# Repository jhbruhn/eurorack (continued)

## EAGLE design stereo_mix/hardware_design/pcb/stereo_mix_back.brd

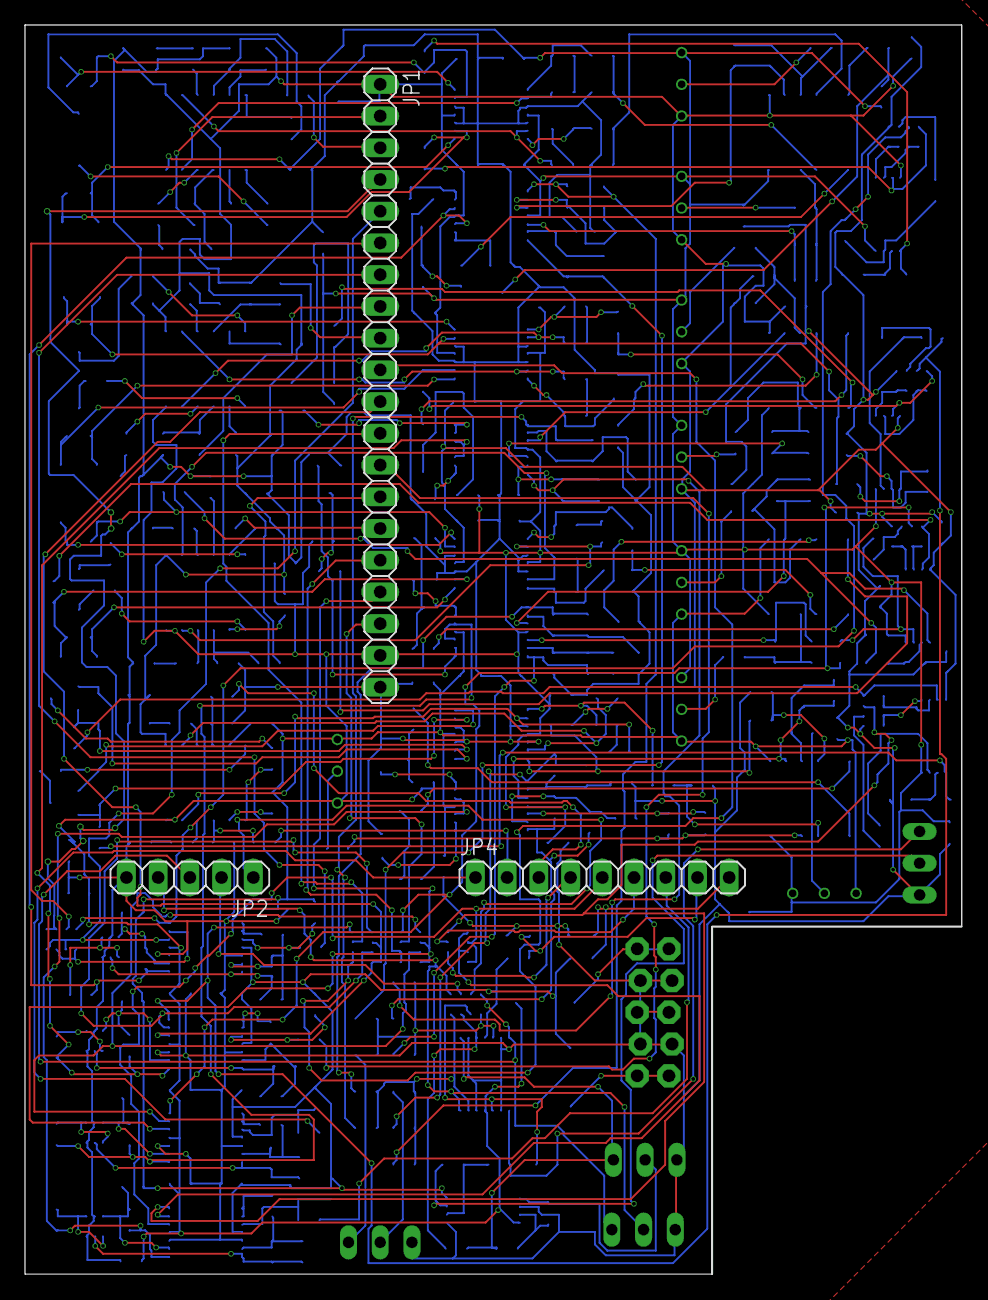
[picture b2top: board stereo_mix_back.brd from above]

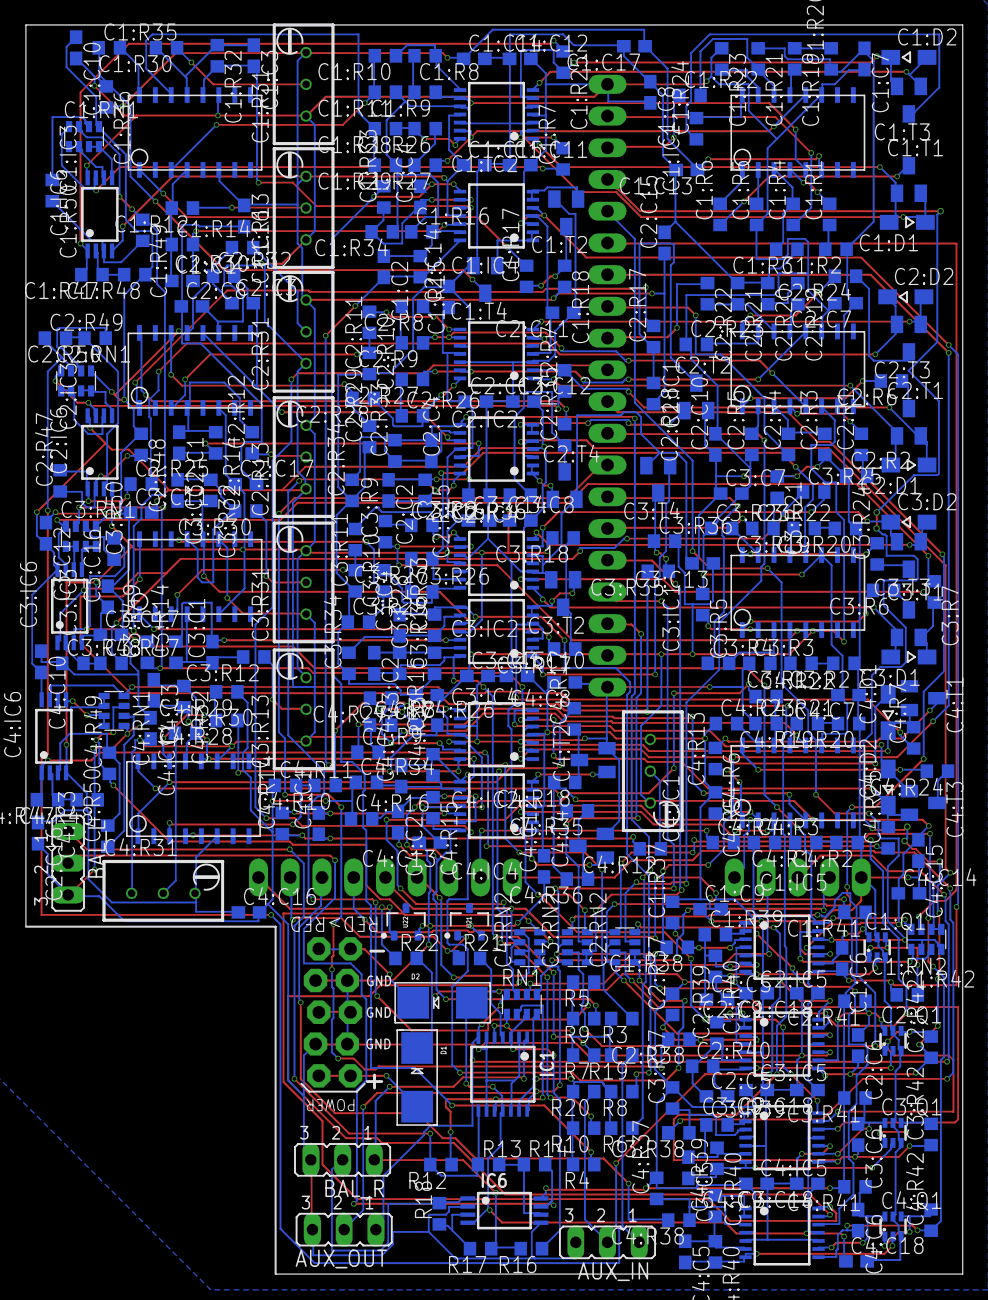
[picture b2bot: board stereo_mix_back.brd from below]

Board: 2 copper layers, 75.0 x 100.0 mm, 349 parts (346 on the bottom side), 271 nets.

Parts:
AUX_IN: JP2
AUX_OUT: JP2
BAL_L: JP2
BAL_R: JP2
C1:C1, C1:C3, C1:C5, C1:C6, C2:C1, C2:C3, C2:C5, C2:C6, C3:C1, C3:C3, C3:C5, C3:C6, C4:C1, C4:C3, C4:C5, C4:C6: 100pF; C0603
C1:C2, C1:C4, C2:C2, C2:C4, C3:C2, C3:C4, C4:C2, C4:C4: 22pF; C0603
C1:C7, C1:C8, C1:C9, C1:C10, C1:C11, C1:C12, C1:C13, C1:C14, C1:C15, C1:C16, C1:C17, C1:C18, C2:C7, C2:C8, C2:C9, C2:C10, C2:C11, C2:C12, C2:C13, C2:C14, C2:C15, C2:C16, C2:C17, C2:C18, C3:C7, C3:C8, C3:C9, C3:C10, C3:C11, C3:C12, C3:C13, C3:C14, C3:C15, C3:C16, C3:C17, C3:C18, C4:C7, C4:C8, C4:C9, C4:C10, C4:C11, C4:C12, C4:C13, C4:C14, C4:C15, C4:C16, C4:C17, C4:C18: 100nF; C0603
C1:D1, C1:D2, C2:D1, C2:D2, C3:D1, C3:D2, C4:D1, C4:D2: 1N4148; SOD323-W
C1:IC1, C1:IC3, C2:IC1, C2:IC3, C3:IC1, C3:IC3, C4:IC1, C4:IC3: LM13700; DMP16
C1:IC2, C1:IC4, C1:IC5, C2:IC2, C2:IC4, C2:IC5, C3:IC2, C3:IC4, C3:IC5, C4:IC2, C4:IC4, C4:IC5: TL084PW; TSSOP14
C1:IC6, C2:IC6, C3:IC6, C4:IC6: TL082PW; TSSOP8
C1:Q1, C2:Q1, C3:Q1, C4:Q1: BC847BS; SOT363_PHILIPS
C1:R1, C1:R19, C2:R1, C2:R19, C3:R1, C3:R19, C4:R1, C4:R19: 22; R0603
C1:R2, C1:R20, C2:R2, C2:R20, C3:R2, C3:R20, C4:R2, C4:R20: 470; R0603
C1:R3, C1:R21, C2:R3, C2:R21, C3:R3, C3:R21, C4:R3, C4:R21: 510; R0603
C1:R4, C1:R22, C2:R4, C2:R22, C3:R4, C3:R22, C4:R4, C4:R22: 21k; R0603
C1:R5, C1:R23, C2:R5, C2:R23, C3:R5, C3:R23, C4:R5, C4:R23: 12k; R0603
C1:R6, C1:R24, C2:R6, C2:R24, C3:R6, C3:R24, C4:R6, C4:R24: 7k2; R0603
C1:R7, C1:R25, C2:R7, C2:R25, C3:R7, C3:R25, C4:R7, C4:R25: 6k8; R0603
C1:R8, C1:R26, C2:R8, C2:R26, C3:R8, C3:R26, C4:R8, C4:R26: 560; R0603
C1:R9, C1:R17, C1:R27, C1:R35, C2:R9, C2:R17, C2:R27, C2:R35, C3:R9, C3:R17, C3:R27, C3:R35, C4:R9, C4:R17, C4:R27, C4:R35: 15k; R0603
C1:R10, C1:R15, C1:R28, C1:R33, C1:R49, C1:R50, C2:R10, C2:R15, C2:R28, C2:R33, C2:R49, C2:R50, C3:R10, C3:R15, C3:R28, C3:R33, C3:R49, C3:R50, C4:R10, C4:R15, C4:R28, C4:R33, C4:R49, C4:R50: 100k; R0603
C1:R11, C1:R29, C2:R11, C2:R29, C3:R11, C3:R29, C4:R11, C4:R29: 680; R0603
C1:R12, C1:R30, C1:R37, C1:R39, C2:R12, C2:R30, C2:R37, C2:R39, C3:R12, C3:R30, C3:R37, C3:R39, C4:R12, C4:R30, C4:R37, C4:R39: 1M; R0603
C1:R13, C1:R31, C2:R13, C2:R31, C3:R13, C3:R31, C4:R13, C4:R31: 100k; RTRIMT93YA
C1:R14, C1:R32, C2:R14, C2:R32, C3:R14, C3:R32, C4:R14, C4:R32: 47k; R0603
C1:R16, C1:R34, C2:R16, C2:R34, C3:R16, C3:R34, C4:R16, C4:R34: 68k; R0603
C1:R18, C1:R36, C2:R18, C2:R36, C3:R18, C3:R36, C4:R18, C4:R36: 680k; R0603
C1:R38, C2:R38, C3:R38, C4:R38: 1k; R0603
C1:R40, C2:R40, C3:R40, C4:R40: 10k; R0603
C1:R41, C2:R41, C3:R41, C4:R41: 10M; R0603
C1:R42, C2:R42, C3:R42, C4:R42: 1k5; R0603
C1:R47, C1:R48, C2:R47, C2:R48, C3:R47, C3:R48, C4:R47, C4:R48: 200k; R0603
C1:RN1, C1:RN2, C2:RN1, C2:RN2, C3:RN1, C3:RN2, C4:RN1, C4:RN2: CTS742C083
C1:T1, C1:T2, C1:T3, C1:T4, C2:T1, C2:T2, C2:T3, C2:T4, C3:T1, C3:T2, C3:T3, C3:T4, C4:T1, C4:T2, C4:T3, C4:T4: 3906; SOT23-BEC
C5: EURO_POWER_LOCKFAT-LOCK; EURO_PWR_HEADER_LOCK
D1, D2: 1N4001; SMADIODE
IC1: TL084PW; TSSOP14
IC6: TL082PW; TSSOP8
JP1: 1X20
JP2: 1X05
JP4: 1X09
R3, R4, R5, R6, R7, R8, R9, R10, R13, R14, R17, R18, R19, R20: 100k; R0603
R12, R16: 24k; R0603
R21: R0603
R22: 680R; R0603
RN1: CTS742C083
U21: TEXAS_INSTRUMENTS_LM4040C5IDBZR; TEXAS_INSTRUMENTS_LM4040C5IDBZR_0
U22: TEXAS_INSTRUMENTS_LM4040C10IDBZR; TEXAS_INSTRUMENTS_LM4040C5IDBZR_0

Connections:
1_IN_L: C1:R4.1, JP1.2
1_IN_R: C1:R22.1, JP1.3
1_PAN_ATT_R: C1:RN2.3, JP1.6
1_PAN_ATT_W: C1:IC5.12, C1:RN2.6, C1:RN2.8, JP1.5
1_PAN_CV_IN: C1:RN2.1, C1:RN2.2, JP1.4
1_VOLUME_CV: C1:R38.2, JP1.7
2_IN_L: C2:R4.1, JP1.8
2_IN_R: C2:R22.1, JP1.9
2_PAN_ATT_R: C2:RN2.3, JP1.12
2_PAN_ATT_W: C2:IC5.12, C2:RN2.6, C2:RN2.8, JP1.11
2_PAN_CV_IN: C2:RN2.1, C2:RN2.2, JP1.10
2_VOLUME_CV: C2:R38.2, JP1.13
3_IN_L: C3:R4.1, JP1.14
3_IN_R: C3:R22.1, JP1.15
3_PAN_ATT_R: C3:RN2.3, JP1.18
3_PAN_ATT_W: C3:IC5.12, C3:RN2.6, C3:RN2.8, JP1.17
3_PAN_CV_IN: C3:RN2.1, C3:RN2.2, JP1.16
3_VOLUME_CV: C3:R38.2, JP4.1
4_IN_L: C4:R4.1, JP4.2
4_IN_R: C4:R22.1, JP4.3
4_PAN_ATT_R: C4:RN2.3, JP4.6
4_PAN_ATT_W: C4:IC5.12, C4:RN2.6, C4:RN2.8, JP4.5
4_PAN_CV_IN: C4:RN2.1, C4:RN2.2, JP4.4
4_VOLUME_CV: C4:R38.2, JP4.7
+12V: C1:C7.2, C1:C8.2, C1:C9.2, C1:C10.2, C1:C11.2, C1:C12.2, C1:IC1.P$11, C1:IC2.4, C1:IC3.P$11, C1:IC4.4, C1:IC5.4, C1:IC6.8, C1:R5.1, C1:R13.1, C1:R23.1, C1:R31.1, C1:R37.2, C1:R41.2, C2:C7.2, C2:C8.2, C2:C9.2, C2:C10.2, C2:C11.2, C2:C12.2, C2:IC1.P$11, C2:IC2.4, C2:IC3.P$11, C2:IC4.4, C2:IC5.4, C2:IC6.8, C2:R5.1, C2:R13.1, C2:R23.1, C2:R31.1, C2:R37.2, C2:R41.2, C3:C7.2, C3:C8.2, C3:C9.2, C3:C10.2, C3:C11.2, C3:C12.2, C3:IC1.P$11, C3:IC2.4, C3:IC3.P$11, C3:IC4.4, C3:IC5.4, C3:IC6.8, C3:R5.1, C3:R13.1, C3:R23.1, C3:R31.1, C3:R37.2, C3:R41.2, C4:C7.2, C4:C8.2, C4:C9.2, C4:C10.2, C4:C11.2, C4:C12.2, C4:IC1.P$11, C4:IC2.4, C4:IC3.P$11, C4:IC4.4, C4:IC5.4, C4:IC6.8, C4:R5.1, C4:R13.1, C4:R23.1, C4:R31.1, C4:R37.2, C4:R41.2, D1.C, IC1.4, IC6.8, JP1.1, R21.2, R22.2
-12V: C1:C13.1, C1:C14.1, C1:C15.1, C1:C16.1, C1:C17.1, C1:C18.1, C1:IC1.P$6, C1:IC2.11, C1:IC3.P$6, C1:IC4.11, C1:IC5.11, C1:IC6.4, C1:R13.3, C1:R18.2, C1:R31.3, C1:R36.2, C2:C13.1, C2:C14.1, C2:C15.1, C2:C16.1, C2:C17.1, C2:C18.1, C2:IC1.P$6, C2:IC2.11, C2:IC3.P$6, C2:IC4.11, C2:IC5.11, C2:IC6.4, C2:R13.3, C2:R18.2, C2:R31.3, C2:R36.2, C3:C13.1, C3:C14.1, C3:C15.1, C3:C16.1, C3:C17.1, C3:C18.1, C3:IC1.P$6, C3:IC2.11, C3:IC3.P$6, C3:IC4.11, C3:IC5.11, C3:IC6.4, C3:R13.3, C3:R18.2, C3:R31.3, C3:R36.2, C4:C13.1, C4:C14.1, C4:C15.1, C4:C16.1, C4:C17.1, C4:C18.1, C4:IC1.P$6, C4:IC2.11, C4:IC3.P$6, C4:IC4.11, C4:IC5.11, C4:IC6.4, C4:R13.3, C4:R18.2, C4:R31.3, C4:R36.2, D2.A, IC1.11, IC6.4, JP1.19
AUX_IN_L: AUX_IN.1, R19.1
AUX_IN_R: AUX_IN.2, R20.1
BAL_N_L: BAL_L.2, IC6.7, R14.2
BAL_N_R: BAL_R.2, IC6.1, R18.2
BAL_P_L: BAL_L.1, IC1.8, R12.2, R13.1
BAL_P_R: BAL_R.1, IC1.1, R16.2, R17.1
BYPASS_L: AUX_OUT.1, IC1.7, JP2.3, RN1.8
BYPASS_R: AUX_OUT.2, IC1.14, JP2.4, RN1.5
C1:N$1: C1:IC1.P$4, C1:R1.2
C1:N$2: C1:R1.1, C1:R2.2
C1:N$3: C1:IC1.P$3, C1:R3.2, C1:R4.2
C1:N$4: C1:IC1.P$1, C1:R6.2
C1:N$5: C1:IC1.P$2, C1:R5.2
C1:N$6: C1:R6.1, C1:T1.C
C1:N$7: C1:D1.A, C1:IC2.1, C1:T1.B
C1:N$8: C1:D1.C, C1:IC2.2, C1:R7.2, C1:T1.E
C1:N$9: C1:IC1.P$5, C1:IC2.9, C1:R9.1
C1:N$10: C1:R8.1, C1:R9.2
C1:N$11: C1:IC2.8, C1:R8.2, C1:R10.1
C1:N$12: C1:C1.1, C1:IC3.P$4, C1:R12.2, C1:R14.1
C1:N$13: C1:IC3.P$3, C1:R10.2, C1:R11.2
C1:N$14: C1:R12.1, C1:R13.2
C1:N$15: C1:C2.1, C1:IC4.13, C1:R15.1, C1:R16.2
C1:N$16: C1:C1.2, C1:IC4.12, C1:R14.2
C1:N$17: C1:IC3.P$1, C1:R17.2
C1:N$18: C1:R17.1, C1:R18.1, C1:T2.C
C1:N$19: C1:IC4.6, C1:IC4.7, C1:T2.B
C1:N$20: C1:IC1.P$13, C1:R19.2
C1:N$21: C1:R19.1, C1:R20.2
C1:N$22: C1:IC1.P$14, C1:R21.2, C1:R22.2
C1:N$23: C1:IC1.P$15, C1:R23.2
C1:N$24: C1:IC1.P$16, C1:R24.2
C1:N$25: C1:R24.1, C1:T3.C
C1:N$26: C1:D2.A, C1:IC2.7, C1:T3.B
C1:N$27: C1:D2.C, C1:IC2.6, C1:R25.2, C1:T3.E
C1:N$28: C1:IC1.P$12, C1:IC2.13, C1:R27.1
C1:N$29: C1:R26.1, C1:R27.2
C1:N$30: C1:IC2.14, C1:R26.2, C1:R28.1
C1:N$31: C1:IC3.P$14, C1:R28.2, C1:R29.2
C1:N$32: C1:C3.1, C1:IC3.P$13, C1:R30.2, C1:R32.1
C1:N$33: C1:R30.1, C1:R31.2
C1:N$34: C1:C3.2, C1:IC3.P$12, C1:IC4.10, C1:R32.2
C1:N$35: C1:C4.1, C1:IC4.9, C1:R33.1, C1:R34.2
C1:N$36: C1:IC3.P$16, C1:R35.2
C1:N$37: C1:R35.1, C1:R36.1, C1:T4.C
C1:N$38: C1:IC4.1, C1:IC4.2, C1:T4.B
C1:N$39: C1:IC5.1, C1:IC5.2, C1:R39.2
C1:N$40: C1:IC5.3, C1:R37.1, C1:R38.1
C1:N$41: C1:C5.1, C1:IC5.6, C1:R39.1, C1:R40.1
C1:N$42: C1:C5.2, C1:IC5.7, C1:Q1.2, C1:R40.2
C1:N$43: C1:IC6.5, C1:RN1.3, C1:RN1.4
C1:N$44: C1:C6.1, C1:IC5.9, C1:Q1.6, C1:R41.1
C1:N$45: C1:IC6.6, C1:RN1.1, C1:RN1.2
C1:N$46: C1:Q1.1, C1:Q1.4, C1:R42.2
C1:N$47: C1:IC6.2, C1:R47.1, C1:R48.2
C1:N$48: C1:IC5.13, C1:RN2.5, C1:RN2.7
C1:N$50: C1:IC6.3, C1:R49.2, C1:R50.2
C1:PAN_CV: C1:IC5.14, C1:R49.1, C1:RN1.7, C1:RN2.4
C1:PAN_CV_L: C1:IC6.7, C1:R7.1, C1:RN1.8
C1:PAN_CV_R: C1:IC6.1, C1:R25.1, C1:R47.2
C1:REF_5: C1:R50.1, C1:RN1.6
C1:VOLUME_CV_LOG: C1:C6.2, C1:IC4.3, C1:IC4.5, C1:IC5.8, C1:R42.1
C2:N$1: C2:IC1.P$4, C2:R1.2
C2:N$2: C2:R1.1, C2:R2.2
C2:N$3: C2:IC1.P$3, C2:R3.2, C2:R4.2
C2:N$4: C2:IC1.P$1, C2:R6.2
C2:N$5: C2:IC1.P$2, C2:R5.2
C2:N$6: C2:R6.1, C2:T1.C
C2:N$7: C2:D1.A, C2:IC2.1, C2:T1.B
C2:N$8: C2:D1.C, C2:IC2.2, C2:R7.2, C2:T1.E
C2:N$9: C2:IC1.P$5, C2:IC2.9, C2:R9.1
C2:N$10: C2:R8.1, C2:R9.2
C2:N$11: C2:IC2.8, C2:R8.2, C2:R10.1
C2:N$12: C2:C1.1, C2:IC3.P$4, C2:R12.2, C2:R14.1
C2:N$13: C2:IC3.P$3, C2:R10.2, C2:R11.2
C2:N$14: C2:R12.1, C2:R13.2
C2:N$15: C2:C2.1, C2:IC4.13, C2:R15.1, C2:R16.2
C2:N$16: C2:C1.2, C2:IC4.12, C2:R14.2
C2:N$17: C2:IC3.P$1, C2:R17.2
C2:N$18: C2:R17.1, C2:R18.1, C2:T2.C
C2:N$19: C2:IC4.6, C2:IC4.7, C2:T2.B
C2:N$20: C2:IC1.P$13, C2:R19.2
C2:N$21: C2:R19.1, C2:R20.2
C2:N$22: C2:IC1.P$14, C2:R21.2, C2:R22.2
C2:N$23: C2:IC1.P$15, C2:R23.2
C2:N$24: C2:IC1.P$16, C2:R24.2
C2:N$25: C2:R24.1, C2:T3.C
C2:N$26: C2:D2.A, C2:IC2.7, C2:T3.B
C2:N$27: C2:D2.C, C2:IC2.6, C2:R25.2, C2:T3.E
C2:N$28: C2:IC1.P$12, C2:IC2.13, C2:R27.1
C2:N$29: C2:R26.1, C2:R27.2
C2:N$30: C2:IC2.14, C2:R26.2, C2:R28.1
C2:N$31: C2:IC3.P$14, C2:R28.2, C2:R29.2
C2:N$32: C2:C3.1, C2:IC3.P$13, C2:R30.2, C2:R32.1
C2:N$33: C2:R30.1, C2:R31.2
C2:N$34: C2:C3.2, C2:IC3.P$12, C2:IC4.10, C2:R32.2
C2:N$35: C2:C4.1, C2:IC4.9, C2:R33.1, C2:R34.2
C2:N$36: C2:IC3.P$16, C2:R35.2
C2:N$37: C2:R35.1, C2:R36.1, C2:T4.C
C2:N$38: C2:IC4.1, C2:IC4.2, C2:T4.B
C2:N$39: C2:IC5.1, C2:IC5.2, C2:R39.2
C2:N$40: C2:IC5.3, C2:R37.1, C2:R38.1
C2:N$41: C2:C5.1, C2:IC5.6, C2:R39.1, C2:R40.1
C2:N$42: C2:C5.2, C2:IC5.7, C2:Q1.2, C2:R40.2
C2:N$43: C2:IC6.5, C2:RN1.3, C2:RN1.4
C2:N$44: C2:C6.1, C2:IC5.9, C2:Q1.6, C2:R41.1
C2:N$45: C2:IC6.6, C2:RN1.1, C2:RN1.2
C2:N$46: C2:Q1.1, C2:Q1.4, C2:R42.2
C2:N$47: C2:IC6.2, C2:R47.1, C2:R48.2
C2:N$48: C2:IC5.13, C2:RN2.5, C2:RN2.7
C2:N$50: C2:IC6.3, C2:R49.2, C2:R50.2
C2:PAN_CV: C2:IC5.14, C2:R49.1, C2:RN1.7, C2:RN2.4
C2:PAN_CV_L: C2:IC6.7, C2:R7.1, C2:RN1.8
C2:PAN_CV_R: C2:IC6.1, C2:R25.1, C2:R47.2
C2:REF_5: C2:R50.1, C2:RN1.6
C2:VOLUME_CV_LOG: C2:C6.2, C2:IC4.3, C2:IC4.5, C2:IC5.8, C2:R42.1
C3:N$1: C3:IC1.P$4, C3:R1.2
C3:N$2: C3:R1.1, C3:R2.2
C3:N$3: C3:IC1.P$3, C3:R3.2, C3:R4.2
C3:N$4: C3:IC1.P$1, C3:R6.2
C3:N$5: C3:IC1.P$2, C3:R5.2
C3:N$6: C3:R6.1, C3:T1.C
C3:N$7: C3:D1.A, C3:IC2.1, C3:T1.B
C3:N$8: C3:D1.C, C3:IC2.2, C3:R7.2, C3:T1.E
C3:N$9: C3:IC1.P$5, C3:IC2.9, C3:R9.1
C3:N$10: C3:R8.1, C3:R9.2
C3:N$11: C3:IC2.8, C3:R8.2, C3:R10.1
C3:N$12: C3:C1.1, C3:IC3.P$4, C3:R12.2, C3:R14.1
C3:N$13: C3:IC3.P$3, C3:R10.2, C3:R11.2
C3:N$14: C3:R12.1, C3:R13.2
C3:N$15: C3:C2.1, C3:IC4.13, C3:R15.1, C3:R16.2
C3:N$16: C3:C1.2, C3:IC4.12, C3:R14.2
C3:N$17: C3:IC3.P$1, C3:R17.2
C3:N$18: C3:R17.1, C3:R18.1, C3:T2.C
C3:N$19: C3:IC4.6, C3:IC4.7, C3:T2.B
C3:N$20: C3:IC1.P$13, C3:R19.2
C3:N$21: C3:R19.1, C3:R20.2
C3:N$22: C3:IC1.P$14, C3:R21.2, C3:R22.2
C3:N$23: C3:IC1.P$15, C3:R23.2
C3:N$24: C3:IC1.P$16, C3:R24.2
C3:N$25: C3:R24.1, C3:T3.C
C3:N$26: C3:D2.A, C3:IC2.7, C3:T3.B
C3:N$27: C3:D2.C, C3:IC2.6, C3:R25.2, C3:T3.E
C3:N$28: C3:IC1.P$12, C3:IC2.13, C3:R27.1
C3:N$29: C3:R26.1, C3:R27.2
C3:N$30: C3:IC2.14, C3:R26.2, C3:R28.1
C3:N$31: C3:IC3.P$14, C3:R28.2, C3:R29.2
C3:N$32: C3:C3.1, C3:IC3.P$13, C3:R30.2, C3:R32.1
C3:N$33: C3:R30.1, C3:R31.2
C3:N$34: C3:C3.2, C3:IC3.P$12, C3:IC4.10, C3:R32.2
C3:N$35: C3:C4.1, C3:IC4.9, C3:R33.1, C3:R34.2
C3:N$36: C3:IC3.P$16, C3:R35.2
C3:N$37: C3:R35.1, C3:R36.1, C3:T4.C
C3:N$38: C3:IC4.1, C3:IC4.2, C3:T4.B
C3:N$39: C3:IC5.1, C3:IC5.2, C3:R39.2
C3:N$40: C3:IC5.3, C3:R37.1, C3:R38.1
C3:N$41: C3:C5.1, C3:IC5.6, C3:R39.1, C3:R40.1
C3:N$42: C3:C5.2, C3:IC5.7, C3:Q1.2, C3:R40.2
C3:N$43: C3:IC6.5, C3:RN1.3, C3:RN1.4
C3:N$44: C3:C6.1, C3:IC5.9, C3:Q1.6, C3:R41.1
C3:N$45: C3:IC6.6, C3:RN1.1, C3:RN1.2
C3:N$46: C3:Q1.1, C3:Q1.4, C3:R42.2
C3:N$47: C3:IC6.2, C3:R47.1, C3:R48.2
C3:N$48: C3:IC5.13, C3:RN2.5, C3:RN2.7
C3:N$50: C3:IC6.3, C3:R49.2, C3:R50.2
C3:PAN_CV: C3:IC5.14, C3:R49.1, C3:RN1.7, C3:RN2.4
C3:PAN_CV_L: C3:IC6.7, C3:R7.1, C3:RN1.8
C3:PAN_CV_R: C3:IC6.1, C3:R25.1, C3:R47.2
C3:REF_5: C3:R50.1, C3:RN1.6
C3:VOLUME_CV_LOG: C3:C6.2, C3:IC4.3, C3:IC4.5, C3:IC5.8, C3:R42.1
C4:N$1: C4:IC1.P$4, C4:R1.2
C4:N$2: C4:R1.1, C4:R2.2
C4:N$3: C4:IC1.P$3, C4:R3.2, C4:R4.2
C4:N$4: C4:IC1.P$1, C4:R6.2
C4:N$5: C4:IC1.P$2, C4:R5.2
C4:N$6: C4:R6.1, C4:T1.C
C4:N$7: C4:D1.A, C4:IC2.1, C4:T1.B
C4:N$8: C4:D1.C, C4:IC2.2, C4:R7.2, C4:T1.E
C4:N$9: C4:IC1.P$5, C4:IC2.9, C4:R9.1
C4:N$10: C4:R8.1, C4:R9.2
C4:N$11: C4:IC2.8, C4:R8.2, C4:R10.1
C4:N$12: C4:C1.1, C4:IC3.P$4, C4:R12.2, C4:R14.1
C4:N$13: C4:IC3.P$3, C4:R10.2, C4:R11.2
C4:N$14: C4:R12.1, C4:R13.2
C4:N$15: C4:C2.1, C4:IC4.13, C4:R15.1, C4:R16.2
C4:N$16: C4:C1.2, C4:IC4.12, C4:R14.2
C4:N$17: C4:IC3.P$1, C4:R17.2
C4:N$18: C4:R17.1, C4:R18.1, C4:T2.C
C4:N$19: C4:IC4.6, C4:IC4.7, C4:T2.B
C4:N$20: C4:IC1.P$13, C4:R19.2
C4:N$21: C4:R19.1, C4:R20.2
C4:N$22: C4:IC1.P$14, C4:R21.2, C4:R22.2
C4:N$23: C4:IC1.P$15, C4:R23.2
C4:N$24: C4:IC1.P$16, C4:R24.2
C4:N$25: C4:R24.1, C4:T3.C
C4:N$26: C4:D2.A, C4:IC2.7, C4:T3.B
C4:N$27: C4:D2.C, C4:IC2.6, C4:R25.2, C4:T3.E
C4:N$28: C4:IC1.P$12, C4:IC2.13, C4:R27.1
C4:N$29: C4:R26.1, C4:R27.2
C4:N$30: C4:IC2.14, C4:R26.2, C4:R28.1
C4:N$31: C4:IC3.P$14, C4:R28.2, C4:R29.2
C4:N$32: C4:C3.1, C4:IC3.P$13, C4:R30.2, C4:R32.1
C4:N$33: C4:R30.1, C4:R31.2
C4:N$34: C4:C3.2, C4:IC3.P$12, C4:IC4.10, C4:R32.2
C4:N$35: C4:C4.1, C4:IC4.9, C4:R33.1, C4:R34.2
C4:N$36: C4:IC3.P$16, C4:R35.2
C4:N$37: C4:R35.1, C4:R36.1, C4:T4.C
C4:N$38: C4:IC4.1, C4:IC4.2, C4:T4.B
C4:N$39: C4:IC5.1, C4:IC5.2, C4:R39.2
C4:N$40: C4:IC5.3, C4:R37.1, C4:R38.1
C4:N$41: C4:C5.1, C4:IC5.6, C4:R39.1, C4:R40.1
C4:N$42: C4:C5.2, C4:IC5.7, C4:Q1.2, C4:R40.2
C4:N$43: C4:IC6.5, C4:RN1.3, C4:RN1.4
C4:N$44: C4:C6.1, C4:IC5.9, C4:Q1.6, C4:R41.1
C4:N$45: C4:IC6.6, C4:RN1.1, C4:RN1.2
C4:N$46: C4:Q1.1, C4:Q1.4, C4:R42.2
C4:N$47: C4:IC6.2, C4:R47.1, C4:R48.2
C4:N$48: C4:IC5.13, C4:RN2.5, C4:RN2.7
C4:N$50: C4:IC6.3, C4:R49.2, C4:R50.2
C4:PAN_CV: C4:IC5.14, C4:R49.1, C4:RN1.7, C4:RN2.4
C4:PAN_CV_L: C4:IC6.7, C4:R7.1, C4:RN1.8
C4:PAN_CV_R: C4:IC6.1, C4:R25.1, C4:R47.2
C4:REF_5: C4:R50.1, C4:RN1.6
C4:VOLUME_CV_LOG: C4:C6.2, C4:IC4.3, C4:IC4.5, C4:IC5.8, C4:R42.1
GND: AUX_IN.3, AUX_OUT.3, BAL_L.3, BAL_R.3, C1:C7.1, C1:C8.1, C1:C9.1, C1:C10.1, C1:C11.1, C1:C12.1, C1:C13.2, C1:C14.2, C1:C15.2, C1:C16.2, C1:C17.2, C1:C18.2, C1:IC2.3, C1:IC2.5, C1:IC2.10, C1:IC2.12, C1:IC5.5, C1:IC5.10, C1:Q1.3, C1:Q1.5, C1:R2.1, C1:R3.1, C1:R11.1, C1:R16.1, C1:R20.1, C1:R21.1, C1:R29.1, C1:R34.1, C1:R48.1, C1:RN1.5, C1:T2.E, C1:T4.E, C2:C7.1, C2:C8.1, C2:C9.1, C2:C10.1, C2:C11.1, C2:C12.1, C2:C13.2, C2:C14.2, C2:C15.2, C2:C16.2, C2:C17.2, C2:C18.2, C2:IC2.3, C2:IC2.5, C2:IC2.10, C2:IC2.12, C2:IC5.5, C2:IC5.10, C2:Q1.3, C2:Q1.5, C2:R2.1, C2:R3.1, C2:R11.1, C2:R16.1, C2:R20.1, C2:R21.1, C2:R29.1, C2:R34.1, C2:R48.1, C2:RN1.5, C2:T2.E, C2:T4.E, C3:C7.1, C3:C8.1, C3:C9.1, C3:C10.1, C3:C11.1, C3:C12.1, C3:C13.2, C3:C14.2, C3:C15.2, C3:C16.2, C3:C17.2, C3:C18.2, C3:IC2.3, C3:IC2.5, C3:IC2.10, C3:IC2.12, C3:IC5.5, C3:IC5.10, C3:Q1.3, C3:Q1.5, C3:R2.1, C3:R3.1, C3:R11.1, C3:R16.1, C3:R20.1, C3:R21.1, C3:R29.1, C3:R34.1, C3:R48.1, C3:RN1.5, C3:T2.E, C3:T4.E, C4:C7.1, C4:C8.1, C4:C9.1, C4:C10.1, C4:C11.1, C4:C12.1, C4:C13.2, C4:C14.2, C4:C15.2, C4:C16.2, C4:C17.2, C4:C18.2, C4:IC2.3, C4:IC2.5, C4:IC2.10, C4:IC2.12, C4:IC5.5, C4:IC5.10, C4:Q1.3, C4:Q1.5, C4:R2.1, C4:R3.1, C4:R11.1, C4:R16.1, C4:R20.1, C4:R21.1, C4:R29.1, C4:R34.1, C4:R48.1, C4:RN1.5, C4:T2.E, C4:T4.E, C5.GND1, C5.GND2, C5.GND3, C5.GND4, C5.GND5, C5.GND6, IC1.2, IC1.6, IC1.9, IC1.12, IC6.2, IC6.5, JP1.20, JP2.5, U21.2, U22.2
unnamed: C1:C2.2, C1:IC4.14, C1:R15.2, R3.1
unnamed: C1:C4.2, C1:IC4.8, C1:R33.2, R4.1
unnamed: IC1.10, R12.1, RN1.2
unnamed: C2:C2.2, C2:IC4.14, C2:R15.2, R5.1
unnamed: C2:C4.2, C2:IC4.8, C2:R33.2, R6.1
unnamed: C3:C2.2, C3:IC4.14, C3:R15.2, R7.1
unnamed: C3:C4.2, C3:IC4.8, C3:R33.2, R8.1
unnamed: C4:C2.2, C4:IC4.14, C4:R15.2, R9.1
unnamed: C4:C4.2, C4:IC4.8, C4:R33.2, R10.1
unnamed: IC1.3, R16.1, RN1.3
unnamed: IC6.3, R17.2, R18.1
unnamed: IC6.6, R13.2, R14.1
unnamed: C5.POS1, C5.POS2, D1.A
unnamed: C5.NEG1, C5.NEG2, D2.C
OUT_L: JP2.1, RN1.7
OUT_R: JP2.2, RN1.6
REF_5: JP4.8, R21.1, U21.1
REF_10: JP4.9, R22.1, U22.1
SUM_L: IC1.5, R3.2, R5.2, R7.2, R9.2, R19.2, RN1.1
SUM_R: IC1.13, R4.2, R6.2, R8.2, R10.2, R20.2, RN1.4

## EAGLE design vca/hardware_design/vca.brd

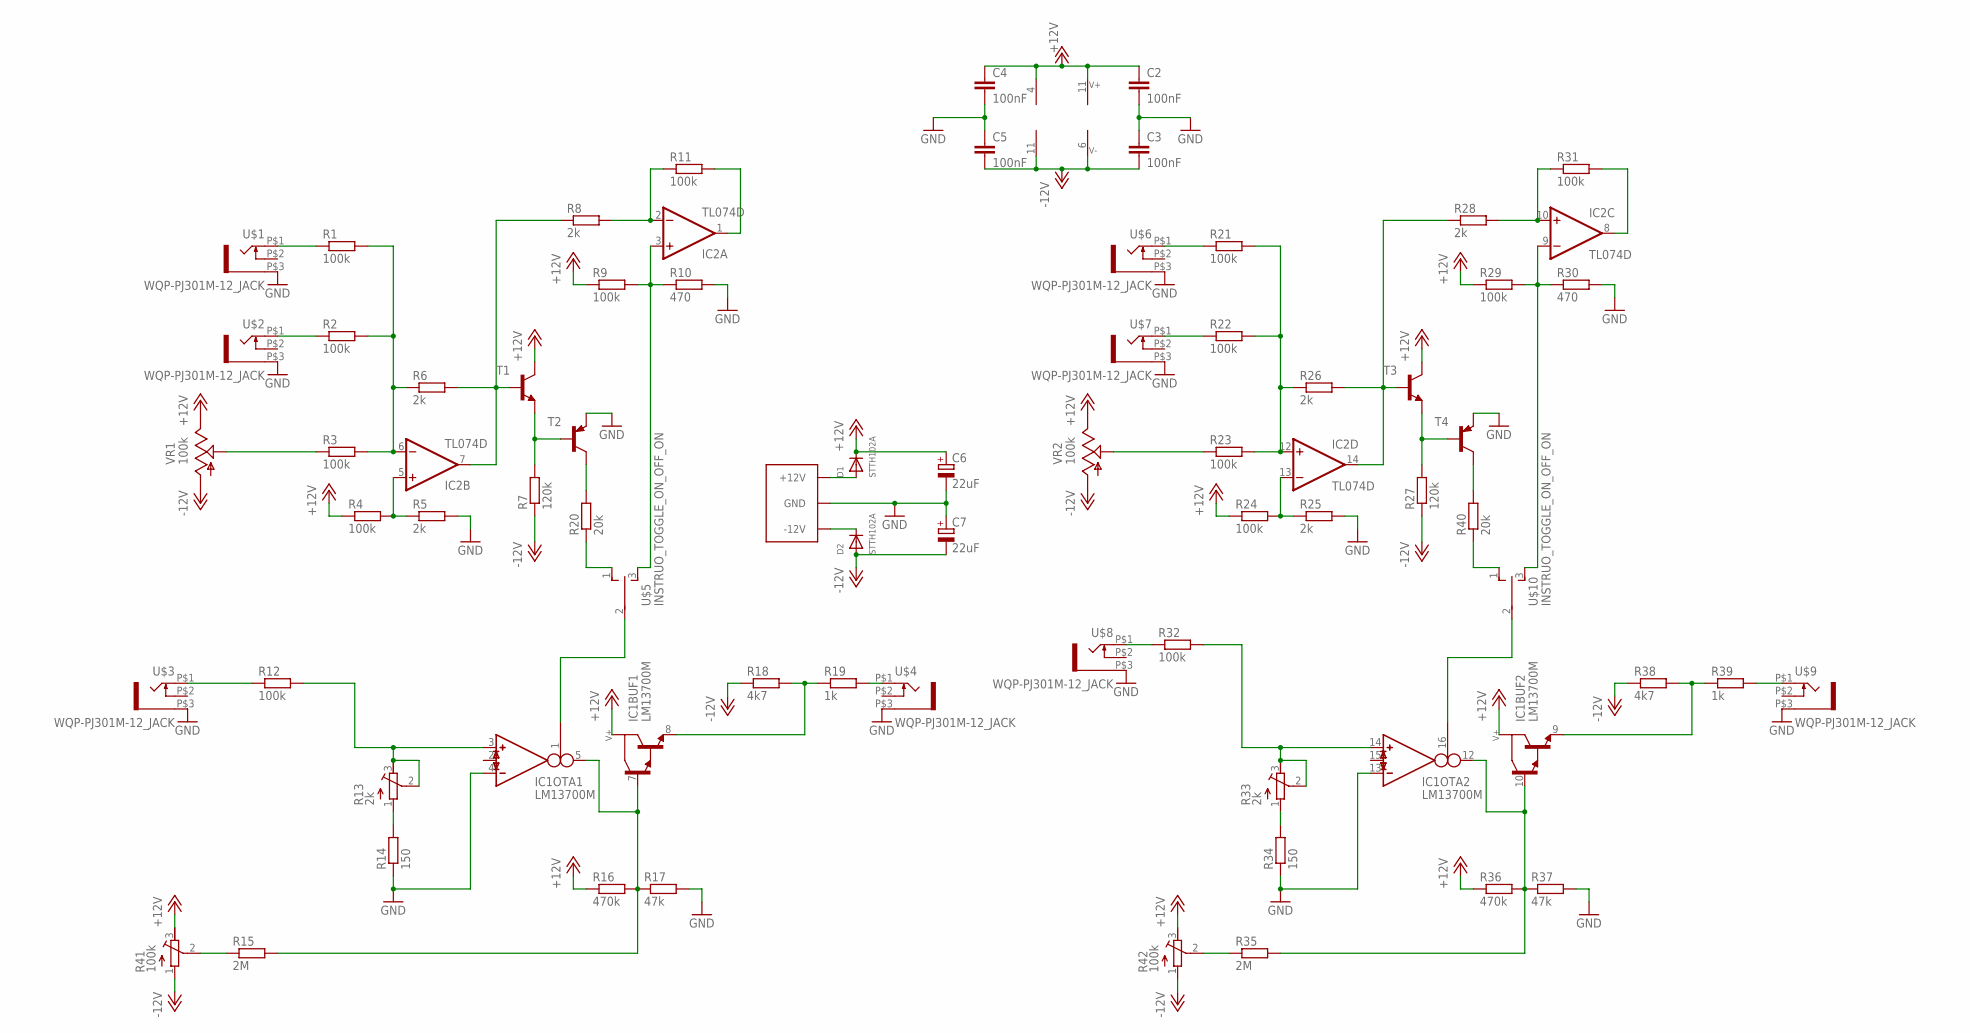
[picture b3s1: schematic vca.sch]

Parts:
C1: EURO_POWER_LOCKFAT-LOCK; EURO_PWR_HEADER_LOCK
C2, C3, C4, C5: 100nF; C0603
C6, C7: 22uF; PANASONIC_C
D1, D2: STTH102A; SMADIODE
IC1: LM13700M; SO16
IC2: TL074D; SO14
R1, R2, R3, R4, R9, R11, R12, R21, R22, R23, R24, R29, R31, R32: 100k; R0603
R5, R6, R8, R25, R26, R28: 2k; R0603
R7, R27: 120k; R0603
R10, R30: 470; R0603
R13, R33: 2k; RTRIM64W
R14, R34: 150; R0603
R15, R35: 2M; R0603
R16, R36: 470k; R0603
R17, R37: 47k; R0603
R18, R38: 4k7; R0603
R19, R39: 1k; R0603
R20, R40: 20k; R0603
R41, R42: 100k; RTRIM64W
T1, T3: MMBT3904LT1-NPN-SOT23-BEC; SOT23-BEC
T2, T4: MMBT3906LT1-PNP-SOT23-BEC; SOT23-BEC
U$1, U$2, U$3, U$4, U$6, U$7, U$8, U$9: WQP-PJ301M-12_JACK
U$5, U$10: INSTRUO_TOGGLE_ON_OFF_ON
VR1, VR2: 100k; 9MM_SNAP-IN_POT

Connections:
+12V: C2.1, C4.1, C6.+, D1.C, IC1.11 (V+), IC2.4 (V+), R4.1, R9.1, R16.1, R24.1, R29.1, R36.1, R41.3 (E), R42.3 (E), T1.C, T3.C, VR1.3 (E), VR2.3 (E)
-12V: C3.2, C5.2, C7.-, D2.A, IC1.6 (V-), IC2.11 (V-), R7.1, R18.1, R27.1, R38.1, R41.1 (A), R42.1 (A), VR1.1 (A), VR2.1 (A)
GND: C1.GND1 (GND), C1.GND2 (GND), C1.GND3 (GND), C1.GND4 (GND), C1.GND5 (GND), C1.GND6 (GND), C2.2, C3.1, C4.2, C5.1, C6.-, C7.+, IC1.4 (IN_N), IC1.13 (IN_N), R5.2, R10.2, R14.1, R17.2, R25.2, R30.2, R34.1, R37.2, T2.E, T4.E, U$1.P$3 (1), U$2.P$3 (1), U$3.P$3 (1), U$4.P$3 (1), U$6.P$3 (1), U$7.P$3 (1), U$8.P$3 (1), U$9.P$3 (1)
unnamed: R1.1, U$1.P$1 (2)
unnamed: R2.1, U$2.P$1 (2)
unnamed: R3.1, VR1.2 (S)
unnamed: IC2.6 (-IN), R1.2, R2.2, R3.2, R6.1
unnamed: IC2.5 (+IN), R4.2, R5.1
unnamed: IC2.7 (OUT), R6.2, R8.1, T1.B
unnamed: IC2.2 (-IN), R8.2, R11.1
unnamed: R7.2, T1.E, T2.B
unnamed: IC2.3 (+IN), R9.2, R10.1, U$5.3 (S)
unnamed: IC1.5 (OUT), IC1.7 (B), R15.2, R16.2, R17.1
unnamed: IC2.1 (OUT), R11.2
unnamed: R12.1, U$3.P$1 (2)
unnamed: IC1.3 (IN_P), R12.2, R13.2 (S), R13.3 (E)
unnamed: R15.1, R41.2 (S)
unnamed: R13.1 (A), R14.2
unnamed: R19.2, U$4.P$1 (2)
unnamed: IC1.8 (E), R18.2, R19.1
unnamed: R20.1, U$5.1 (O)
unnamed: IC1.1 (I_BIAS), U$5.2
unnamed: R20.2, T2.C
unnamed: R21.1, U$6.P$1 (2)
unnamed: R22.1, U$7.P$1 (2)
unnamed: R23.1, VR2.2 (S)
unnamed: IC2.12 (+IN), R21.2, R22.2, R23.2, R26.1
unnamed: IC2.13 (-IN), R24.2, R25.1
unnamed: IC2.14 (OUT), R26.2, R28.1, T3.B
unnamed: R27.2, T3.E, T4.B
unnamed: IC2.10 (+IN), R28.2, R31.1
unnamed: IC2.9 (-IN), R29.2, R30.1, U$10.3 (S)
unnamed: IC2.8 (OUT), R31.2
unnamed: IC1.10 (B), IC1.12 (OUT), R35.2, R36.2, R37.1
unnamed: R32.1, U$8.P$1 (2)
unnamed: IC1.14 (IN_P), R32.2, R33.2 (S), R33.3 (E)
unnamed: R33.1 (A), R34.2
unnamed: R35.1, R42.2 (S)
unnamed: R39.2, U$9.P$1 (2)
unnamed: IC1.9 (E), R38.2, R39.1
unnamed: R40.2, T4.C
unnamed: R40.1, U$10.1 (O)
unnamed: IC1.16 (I_BIAS), U$10.2
unnamed: C1.NEG1 (-12V), C1.NEG2 (-12V), D2.C
unnamed: C1.POS1 (+12V), C1.POS2 (+12V), D1.A

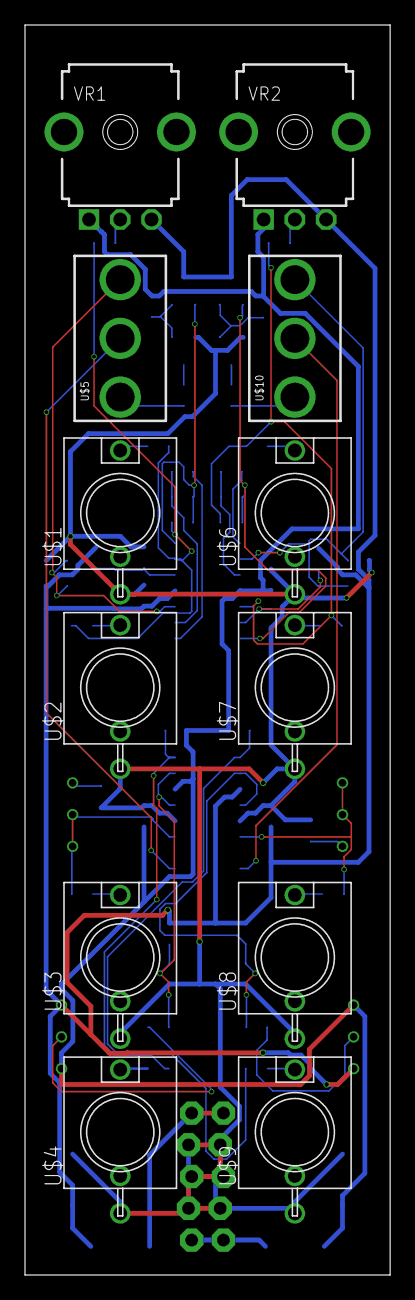
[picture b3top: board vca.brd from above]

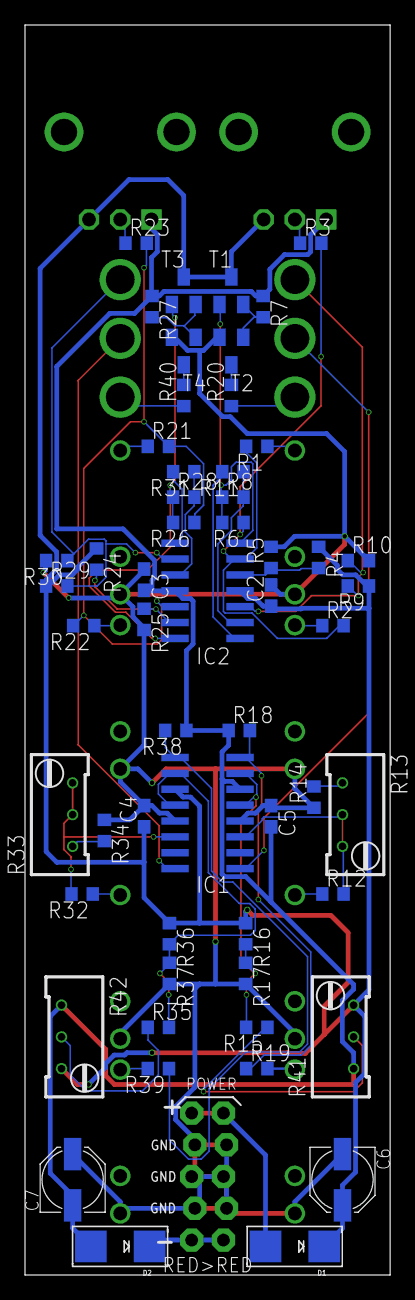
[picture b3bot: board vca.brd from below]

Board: 2 copper layers, 29.2 x 100.0 mm, 69 parts (57 on the bottom side), 45 nets.
